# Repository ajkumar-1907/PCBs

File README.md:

<div align="center">

# 🔌 PCBs

**Small boards, wearable gadgets and electronics experiments, designed in KiCad by [Anuj Kumar](https://github.com/ajkumar-1907).**

</div>

---

## 🗂️ Projects

<table>
<tr>
<td width="260" align="center">

</td>
<td>

### [✨ Cassiopeia Star Hairclip](cassiopeia-star-hairclip/)
A puffy star-shaped hair clip PCB. The Cassiopeia constellation's five LEDs twinkle, driven by a TLC555 timer and powered by a CR2032 coin cell.

`TLC555` · `wearable` · `all-SMD` · `2-layer` · `40 × 42 mm`

</td>
</tr>
</table>

---

## 📐 Repo layout

Each project lives in its own folder:

```
<project>/
├── kicad/         KiCad project, schematic, PCB
├── fabrication/   Gerbers zip, drill files, BOM, pick-and-place
├── images/        3D renders, layout, schematic
└── README.md
```

<div align="center"><sub>More boards coming soon ⚡</sub></div>

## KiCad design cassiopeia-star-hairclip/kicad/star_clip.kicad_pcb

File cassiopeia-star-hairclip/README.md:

<div align="center">

# ✨ Cassiopeia Star Hairclip

**A wearable PCB that blinks the Cassiopeia constellation, made as a birthday gift.**

</div>

---

## 🌟 What it is

A puffy, rounded star-shaped PCB that clips into your hair. The five stars of **Cassiopeia** (the "W") are yellow LEDs joined by exposed silver traces. A **TLC555** timer makes them twinkle about once a second, and a **CR2032** coin cell on the back powers it.

The traces that draw the constellation are also part of the circuit: they're the 555's output net, so every LED cathode connects through them.

<table>
<tr>
<td align="center"><br><sub><b>Front</b>: LEDs, timer, constellation</sub></td>
<td align="center"><br><sub><b>Back</b>: CR2032 holder</sub></td>
</tr>
<tr>
<td align="center"><br><sub><b>Layout</b> in KiCad</sub></td>
<td align="center"><br><sub><b>Concept render</b>: pastel mask + silver HASL</sub></td>
</tr>
</table>

<p align="center">

<br><sub>Side profiles: about 1 mm board plus the coin cell holder</sub>
</p>

---

## ⚡ How it works

| Block | What it does |
|---|---|
| **U1 · TLC555** | CMOS 555 timer in astable mode. Its low quiescent current suits a coin cell. |
| **R6 · R7 · C1** | Set the blink rate: f ≈ 1.44 / ((R6 + 2·R7)·C1) ≈ **1 Hz** |
| **D1–D5 + R1–R5** | Five yellow LEDs, each with its own 470 Ω resistor. They light while OUT is low. |
| **C3 · C4** | Supply decoupling (100 nF + 10 µF). |
| **C2** | Decouples the 555's CONT pin. |
| **TP1–TP4** | Round test pads for OUT, THRES, VDD and GND. |
| **BT1** | Keystone 3034 SMD CR2032 holder on the back. |

> 💡 **Why yellow LEDs?** A CR2032 gives about 3 V. White and blue LEDs need about 3 V themselves, so they'd barely glow. Yellow, amber and red (Vf ≈ 2 V) run bright.

### The constellation

| LED | Star | Name |
|---|---|---|
| D1 | ε Cas | Segin |
| D2 | δ Cas | Ruchbah |
| D3 | γ Cas | Navi |
| D4 | α Cas | Schedar |
| D5 | β Cas | Caph |

---

## 🛠️ Build it yourself

### 1 · Order the board
Upload [`fabrication/star_clip_gerbers.zip`](fabrication/star_clip_gerbers.zip) to any PCB fab.

| Setting | Value |
|---|---|
| Layers | 2 |
| Thickness | **1.0 mm** (lighter in hair) |
| Solder mask | Pastel / light blue (ask the fab), or white |
| Silkscreen | White |
| Surface finish | **Lead-free HASL** (keeps the lines silver) |

### 2 · Parts list

| Ref | Part | Package | Qty |
|---|---|---|---|
| U1 | TLC555CDR timer | SOIC-8 | 1 |
| D1–D5 | Yellow LED | 0805 | 5 |
| R1–R5 | 470 Ω | 0603 | 5 |
| R6 | 10 kΩ | 0603 | 1 |
| R7 | 680 kΩ | 0603 | 1 |
| C1 | 1 µF | 0603 | 1 |
| C2 | 10 nF | 0603 | 1 |
| C3 | 100 nF | 0603 | 1 |
| C4 | 10 µF | 0805 | 1 |
| BT1 | Keystone 3034 CR2032 holder | SMD | 1 |
| — | CR2032 cell + metal snap/alligator hair clip | — | 1 |

JLCPCB-style [`BOM_JLC.csv`](fabrication/BOM_JLC.csv) and [`CPL_JLC.csv`](fabrication/CPL_JLC.csv) are included if you want it assembled. Add the LCSC part numbers to the BOM first.

### 3 · Solder & assemble
1. Solder the front parts first: the 555, then the passives, then the LEDs. **Watch LED polarity**: the cathode goes to the silver constellation line.
2. Flip the board and solder the CR2032 holder to the back.
3. Pop in a CR2032 and it should start blinking.
4. Glue a metal hair clip across the back with epoxy or E6000.

---

## 🎛️ Tweaks

| Want… | Change |
|---|---|
| Slower twinkle | C1 → 2.2 µF |
| Faster twinkle | C1 → 470 nF |
| Brighter LEDs | R1–R5 → 330 Ω |
| Longer battery life | R1–R5 → 1 kΩ |
| Turn it off | Remove the coin cell |

---

## 📁 Files

```
cassiopeia-star-hairclip/
├── kicad/
│   ├── star_clip.kicad_pro      ← open this in KiCad 10
│   ├── star_clip.kicad_sch
│   ├── star_clip.kicad_pcb
│   └── schematic.pdf
├── fabrication/
│   ├── star_clip_gerbers.zip    ← upload this to the fab
│   ├── gerbers/                 (individual Gerber + drill files)
│   ├── BOM_JLC.csv
│   └── CPL_JLC.csv
└── images/
```

---

<div align="center">

Designed by **[Anuj Kumar](https://github.com/ajkumar-1907)** · Electrical Engineering @ DTU

<sub>Inspired by a star-hairclip build video I came across. This layout, circuit and constellation placement were drawn from scratch in KiCad.</sub>

⭐ If you build one, star the repo!

</div>

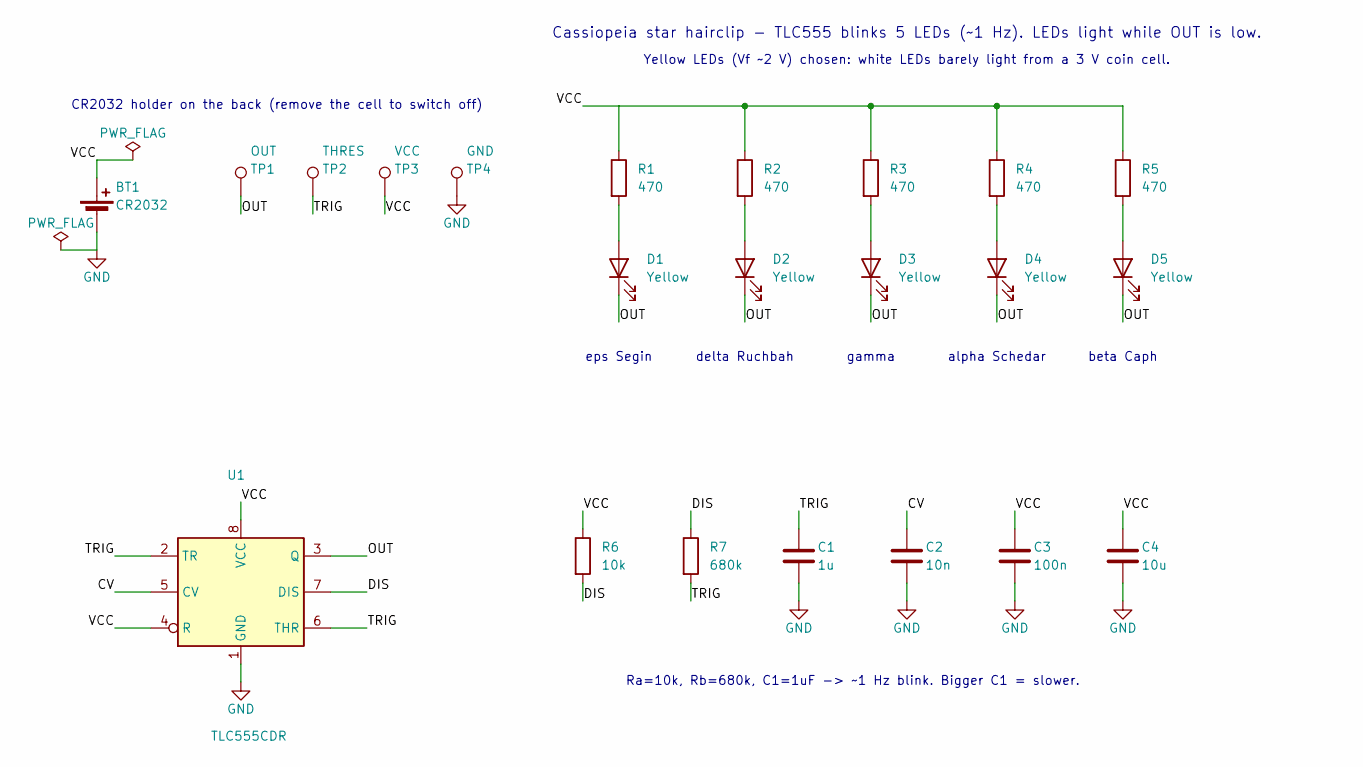
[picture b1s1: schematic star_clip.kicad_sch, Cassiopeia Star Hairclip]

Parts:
BT1: CR2032; BatteryHolder_Keystone_3034_1x20mm
C1: 1u; C_0603_1608Metric
C2: 10n; C_0603_1608Metric
C3: 100n; C_0603_1608Metric
C4: 10u; C_0805_2012Metric
D1, D2, D3, D4, D5: Yellow; LED_0805_2012Metric
R1, R2, R3, R4, R5: 470; R_0603_1608Metric
R6: 10k; R_0603_1608Metric
R7: 680k; R_0603_1608Metric
TP1: OUT; TestPoint_Pad_D1.5mm
TP2: THRES; TestPoint_Pad_D1.5mm
TP3: VCC; TestPoint_Pad_D1.5mm
TP4: GND; TestPoint_Pad_D1.5mm
U1: TLC555CDR; SOIC-8_3.9x4.9mm_P1.27mm

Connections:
/CV: C2.1, U1.5 (CV)
/DIS: R6.2, R7.1, U1.7 (DIS)
/OUT: D1.1 (K), D2.1 (K), D3.1 (K), D4.1 (K), D5.1 (K), TP1.1, U1.3 (Q)
/TRIG: C1.1, R7.2, TP2.1, U1.2 (TR), U1.6 (THR)
/VCC: BT1.1 (+), C3.1, C4.1, R1.1, R2.1, R3.1, R4.1, R5.1, R6.1, TP3.1, U1.4 (R), U1.8 (VCC)
GND: BT1.2 (-), C1.2, C2.2, C3.2, C4.2, TP4.1, U1.1 (GND)
unnamed: D1.2 (A), R1.2
unnamed: D2.2 (A), R2.2
unnamed: D3.2 (A), R3.2
unnamed: D4.2 (A), R4.2
unnamed: D5.2 (A), R5.2

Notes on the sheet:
eps Segin
gamma
alpha Schedar
Yellow LEDs (Vf ~2 V) chosen: white LEDs barely light from a 3 V coin cell.
Ra=10k, Rb=680k, C1=1uF -> ~1 Hz blink. Bigger C1 = slower.
CR2032 holder on the back (remove the cell to switch off)
delta Ruchbah
Cassiopeia star hairclip - TLC555 blinks 5 LEDs (~1 Hz). LEDs light while OUT is low.
beta Caph

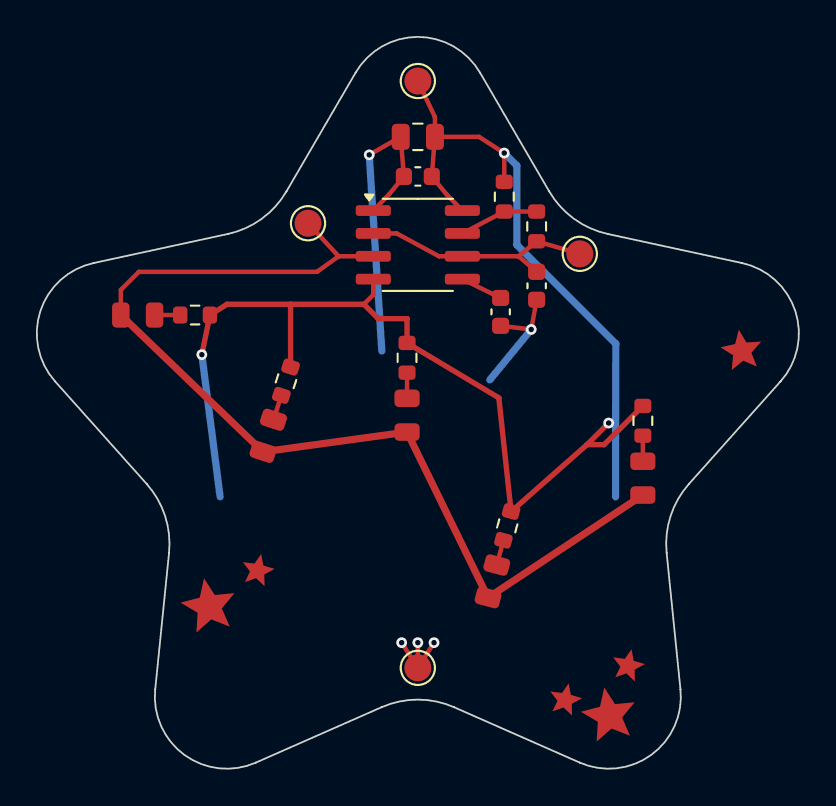
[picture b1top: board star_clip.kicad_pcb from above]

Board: 2 copper layers, 42.3 x 40.7 mm, 22 parts (1 on the bottom side), 11 nets.

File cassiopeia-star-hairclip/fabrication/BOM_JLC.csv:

Comment,Designator,Footprint,Qty,LCSC Part #
Keystone 3034 CR2032 SMD holder (bottom side),BT1,BatteryHolder_Keystone_3034_1x20mm,1,
Capacitor 1uF X7R 0603,C1,C_0603_1608Metric,1,
Capacitor 10nF X7R 0603,C2,C_0603_1608Metric,1,
Capacitor 100nF X7R 0603,C3,C_0603_1608Metric,1,
Capacitor 10uF X5R 0805,C4,C_0805_2012Metric,1,
LED yellow 0805 (Vf ~2 V),"D1,D2,D3,D4,D5",LED_0805_2012Metric,5,
Resistor 470R 1% 0603,"R1,R2,R3,R4,R5",R_0603_1608Metric,5,
Resistor 10k 1% 0603,R6,R_0603_1608Metric,1,
Resistor 680k 1% 0603,R7,R_0603_1608Metric,1,
"TI TLC555CDR CMOS timer, SOIC-8",U1,SOIC-8_3.9x4.9mm_P1.27mm,1,
